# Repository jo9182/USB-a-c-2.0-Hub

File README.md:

# USB-A & C USB Hub
For Hackclub's Blueprint YSWS.

Made this because I though "what would be easy?" and was terribly mistaken! At least I've learned a LOT about EasyEDA and working with PCBs! Also, I have an uncomfortable amount of knowledge about USB-C ports now... eugh.

---
## Project Overview

This has been my second time doing anything like this, and it's my first time using EasyEDA to fully design and make something. As much as I loved EasyEDA, I can now say I prefer KiCAD! Now, if only KiCAD were as convenient with libraries...

### Features

This things got two cutting-edge (I'm joking, this is all USB 2.0) USB-A ports and two USB-C ports. There's also a dashing little dragon on the top along with my usual username!

### Included Files (what's in /PCB/)

I put both available BOM options in since I wasn't sure which would be preferred.
* BOM.xlsx
* BOM.csv
* Gerber.zip
* The Unzipped contents of Gerber.zip in the PCB/Gerber/ directory
* PickAndPlace.xlsx

Schematic            |
:-------------------------:|

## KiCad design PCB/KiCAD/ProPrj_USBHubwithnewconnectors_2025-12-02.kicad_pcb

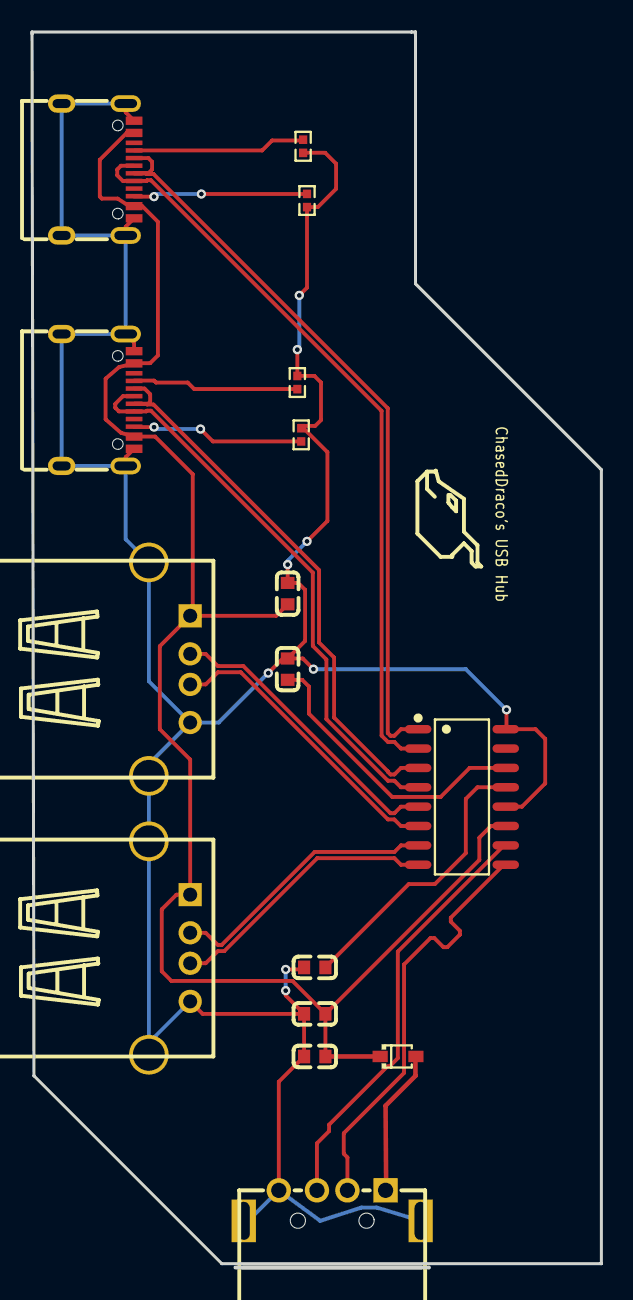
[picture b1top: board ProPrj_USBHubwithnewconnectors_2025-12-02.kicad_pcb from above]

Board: 2 copper layers, 37.3 x 80.8 mm, 16 parts (0 on the bottom side), 19 nets.

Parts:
C1, C2, C3, C4, C5: C0603
D1: SOD-323_L1.8-W1.3-LS2.5-RD
R1, R2, R3, R4: R0402
U1: SOP-16_L10.0-W3.9-P1.27-LS6.0-BL
USB1: USB-A-TH_U-G-04WD-W-01
USB2, USB3: USB-A-TH_C46407
USB4, USB5: USB-C-SMD_TYPE-C-6PIN-2MD-073

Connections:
$1N1: U1.10, USB1.3
$1N2: U1.9, USB1.2
$1N3: U1.7, USB3.2
$1N4: U1.8, USB3.3
$1N5: U1.6, USB2.3
$1N6: U1.5, USB2.2
$1N11: C4.1, U1.14
$1N12: C5.1, U1.13
$1N14: U1.3, USB4.5, USB4.7
$1N15: U1.4, USB4.6, USB4.8
$1N16: U1.2, USB5.6, USB5.8
$1N17: U1.1, USB5.5, USB5.7
$1N19: R2.1, USB4.10
$1N444: D1.2, USB1.1
$1N467: R1.1, USB4.4
$1N478: R3.2, USB5.4
$1N479: R4.2, USB5.10
+5V: C1.1, C2.1, C3.1, D1.1, U1.11, USB2.1, USB3.1, USB4.2, USB4.11, USB5.2, USB5.11
GND: C1.2, C2.2, C3.2, C4.2, C5.2, R1.2, R2.2, R3.1, R4.1, U1.12, U1.16, USB1.4, USB1.5, USB1.6, USB2.4, USB2.5, USB2.6, USB3.4, USB3.5, USB3.6, USB4.1, USB4.12, USB4.13, USB4.14, USB5.1, USB5.12, USB5.13, USB5.14

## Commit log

2025-12-02 Fix up title
2025-12-02 relevant info for readme
    Added project overview, features, and included files sections.
2025-12-02 make PCB directory
2025-12-02 The BOM scares me
    So I hope it works
2025-12-02 Files are listed now
2025-12-02 i forgor
2025-12-02 Little more personal insight
2025-12-02 Make Gerber Directory
2025-12-02 Everything from Gerber.zip
2025-12-02 Schematic and Gerber contents
2025-12-02 Make KiCAD directory
2025-12-02 Everything from KiCAD after import
2025-12-02 Footprint and library files
